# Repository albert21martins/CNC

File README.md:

# CNC
this is a project based on Cyclone PCB Factory https://github.com/carlosgs/Cyclone-PCB-Factory
Changed the hardware (MSP430) & Software. Add a 3.2"TFT User Interface and SD card in order to be independet from PC.
Still a lot to do. This is the first version and there are still some things to change in software.
You can find more information here:
http://e-homelab.flyvotech.com/index.php/2015/10/07/cnc-milling-machine/

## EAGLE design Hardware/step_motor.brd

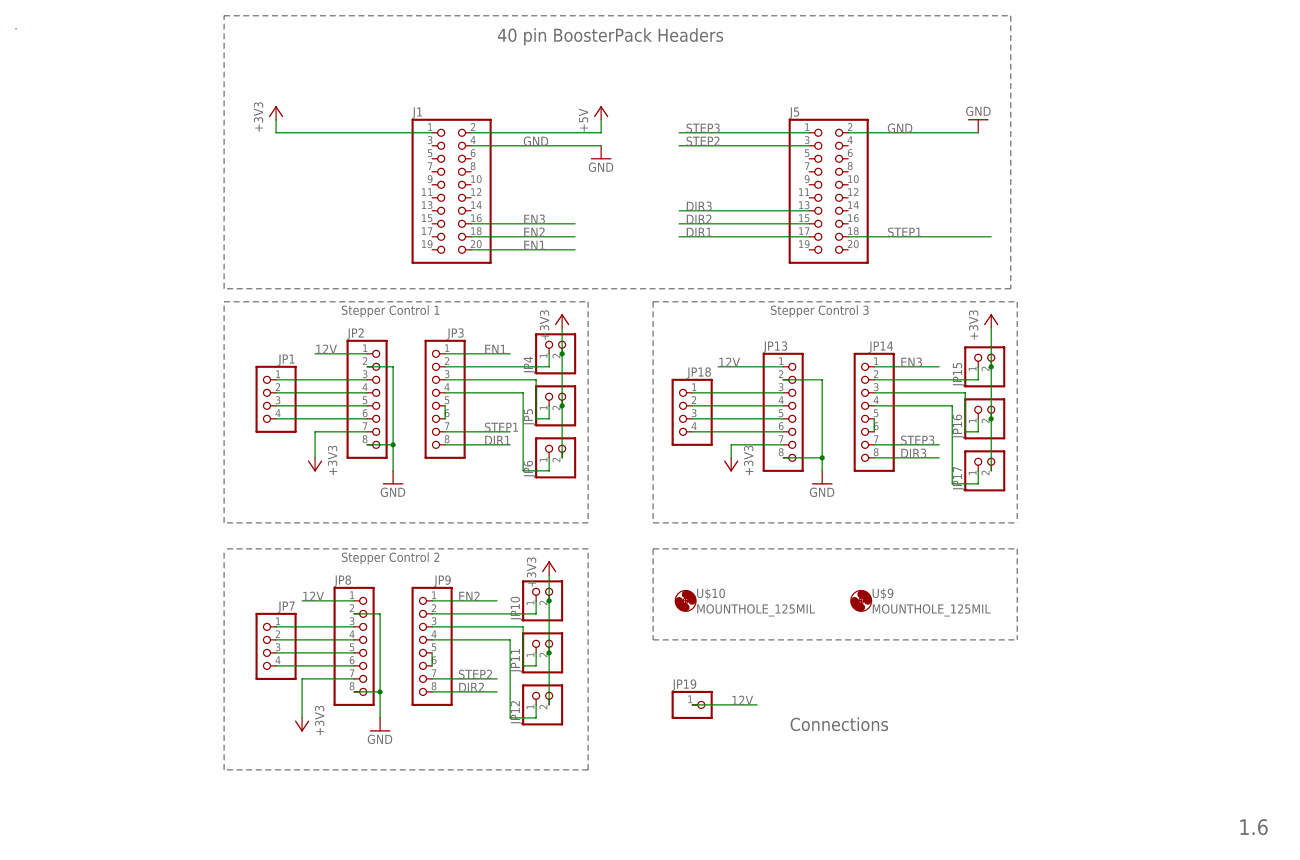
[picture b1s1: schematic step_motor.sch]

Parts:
J1, J5: PINHD-2X10; 2X10
JP1, JP7, JP18: PINHD-1X4; 1X04
JP2, JP3, JP8, JP9, JP13, JP14: PINHD-1X8; 1X08
JP4, JP5, JP6, JP10, JP11, JP12, JP15, JP16, JP17: PINHD-1X2; 1X02
JP19: PINHD-1X1; 1X01
U$4: MS_TM
U$9, U$10: MOUNTHOLE_125MIL

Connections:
12V: JP2.1, JP8.1, JP13.1, JP19.1
+5V: J1.2
DIR1: J5.17, JP3.8
DIR2: J5.15, JP9.8
DIR3: J5.13, JP14.8
EN1: J1.20, JP3.1
EN2: J1.18, JP9.1
EN3: J1.16, JP14.1
GND: J1.4, J5.2, JP2.2, JP2.8, JP8.2, JP8.8, JP13.2, JP13.8
unnamed: JP1.1, JP2.3
unnamed: JP1.2, JP2.4
unnamed: JP1.3, JP2.5
unnamed: JP1.4, JP2.6
unnamed: JP3.5, JP3.6
unnamed: JP3.2, JP4.1
unnamed: JP3.3, JP5.1
unnamed: JP3.4, JP6.1
unnamed: JP9.2, JP10.1
unnamed: JP9.3, JP11.1
unnamed: JP9.4, JP12.1
unnamed: JP7.1, JP8.3
unnamed: JP7.2, JP8.4
unnamed: JP9.5, JP9.6
unnamed: JP7.3, JP8.5
unnamed: JP7.4, JP8.6
unnamed: JP14.2, JP15.1
unnamed: JP14.3, JP16.1
unnamed: JP14.4, JP17.1
unnamed: JP14.5, JP14.6
unnamed: JP13.3, JP18.1
unnamed: JP13.4, JP18.2
unnamed: JP13.5, JP18.3
unnamed: JP13.6, JP18.4
STEP1: J5.18, JP3.7
STEP2: J5.3, JP9.7
STEP3: J5.1, JP14.7
VCC2: J1.1, JP2.7, JP4.2, JP5.2, JP6.2, JP8.7, JP10.2, JP11.2, JP12.2, JP13.7, JP15.2, JP16.2, JP17.2

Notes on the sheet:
40 pin BoosterPack Headers
Connections
1.6
Stepper Control 1
Stepper Control 2
Stepper Control 3

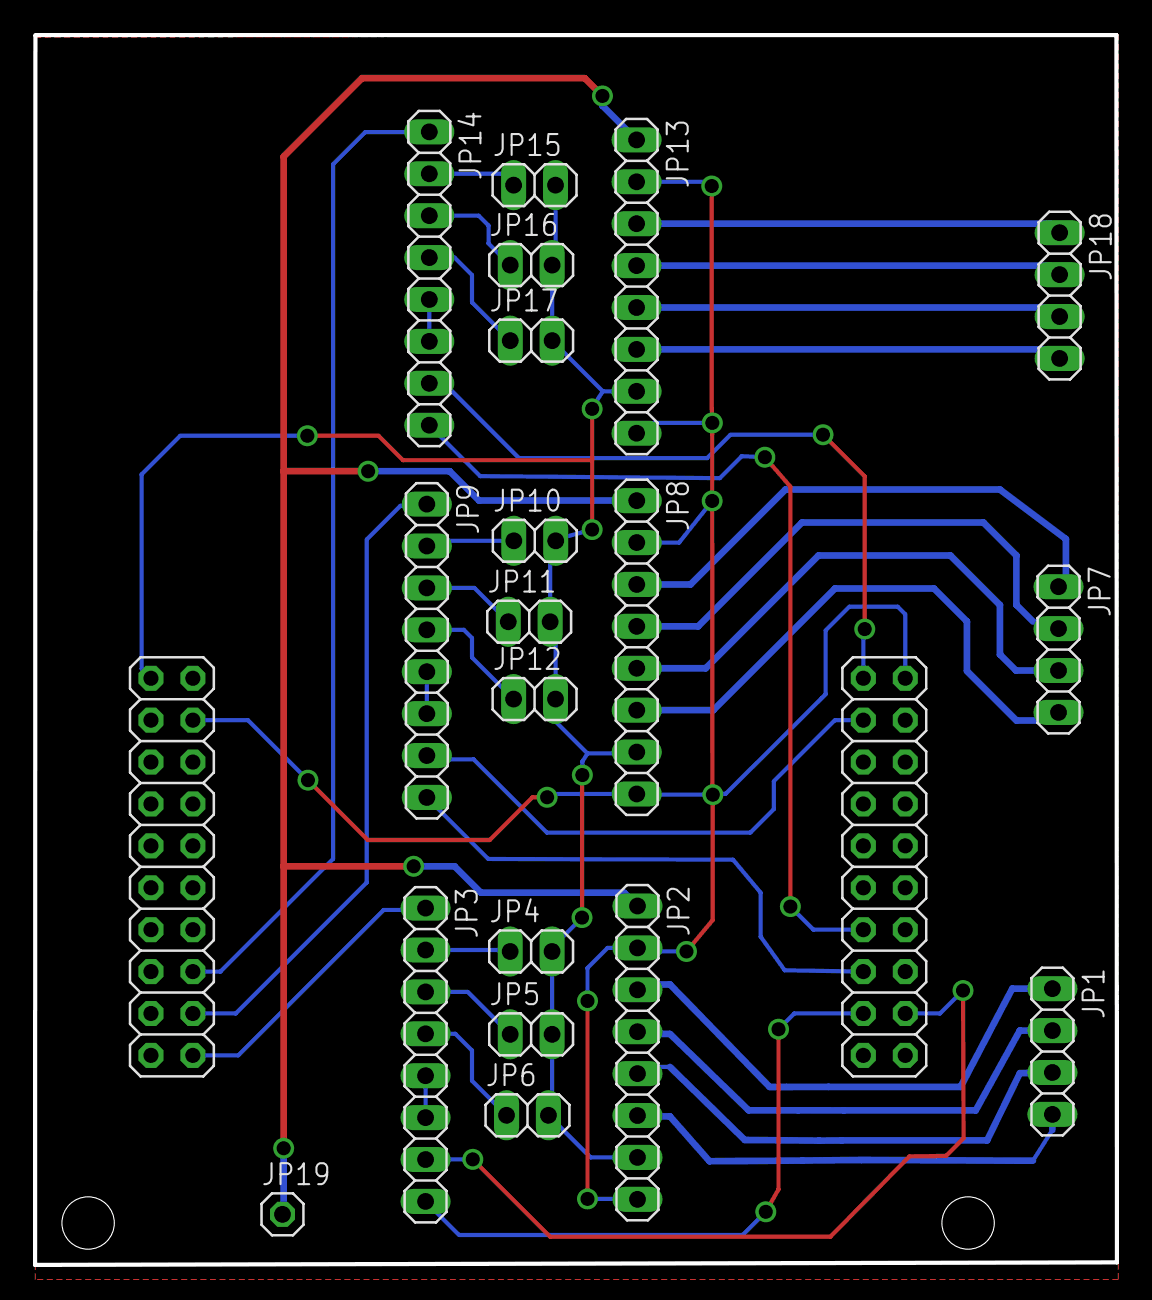
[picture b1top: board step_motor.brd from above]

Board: 2 copper layers, 65.6 x 74.5 mm, 24 parts (0 on the bottom side), 36 nets.

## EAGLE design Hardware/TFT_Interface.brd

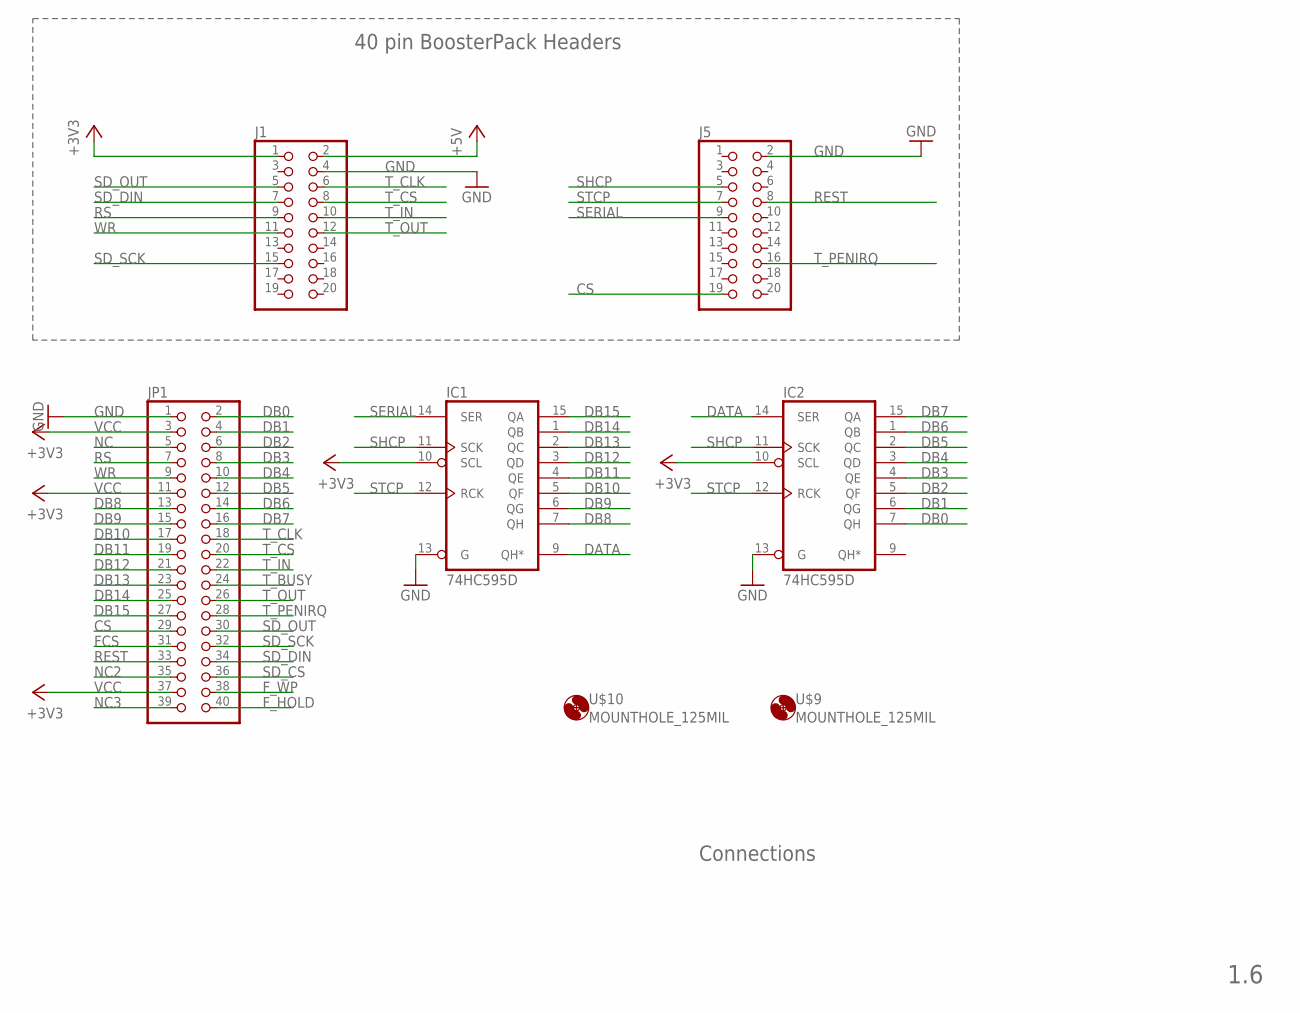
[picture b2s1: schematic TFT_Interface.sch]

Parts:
IC1, IC2: 74HC595D; SO16
J1, J5: PINHD-2X10; 2X10
JP1: PINHD-2X20; 2X20
U$9, U$10: MOUNTHOLE_125MIL

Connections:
+5V: J1.2
CS: J5.19, JP1.29
DATA: IC1.9 (QH*), IC2.14 (SER)
DB0: IC2.7 (QH), JP1.2
DB1: IC2.6 (QG), JP1.4
DB2: IC2.5 (QF), JP1.6
DB3: IC2.4 (QE), JP1.8
DB4: IC2.3 (QD), JP1.10
DB5: IC2.2 (QC), JP1.12
DB6: IC2.1 (QB), JP1.14
DB7: IC2.15 (QA), JP1.16
DB8: IC1.7 (QH), JP1.13
DB9: IC1.6 (QG), JP1.15
DB10: IC1.5 (QF), JP1.17
DB11: IC1.4 (QE), JP1.19
DB12: IC1.3 (QD), JP1.21
DB13: IC1.2 (QC), JP1.23
DB14: IC1.1 (QB), JP1.25
DB15: IC1.15 (QA), JP1.27
FCS: JP1.31
F_HOLD: JP1.40
F_WP: JP1.38
GND: IC1.8 (GND), IC1.13 (G), IC2.8 (GND), IC2.13 (G), J1.4, J5.2, JP1.1
NC: JP1.5
NC2: JP1.35
NC3: JP1.39
REST: J5.8, JP1.33
RS: J1.9, JP1.7
SD_CS: JP1.36
SD_DIN: J1.7, JP1.34
SD_OUT: J1.5, JP1.30
SD_SCK: J1.15, JP1.32
SERIAL: IC1.14 (SER), J5.9
SHCP: IC1.11 (SCK), IC2.11 (SCK), J5.5
STCP: IC1.12 (RCK), IC2.12 (RCK), J5.7
T_BUSY: JP1.24
T_CLK: J1.6, JP1.18
T_CS: J1.8, JP1.20
T_IN: J1.10, JP1.22
T_OUT: J1.12, JP1.26
T_PENIRQ: J5.16, JP1.28
VCC: IC1.10 (SCL), IC1.16 (VCC), IC2.10 (SCL), IC2.16 (VCC), J1.1, JP1.3, JP1.11, JP1.37
WR: J1.11, JP1.9

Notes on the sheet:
40 pin BoosterPack Headers
Connections
1.6

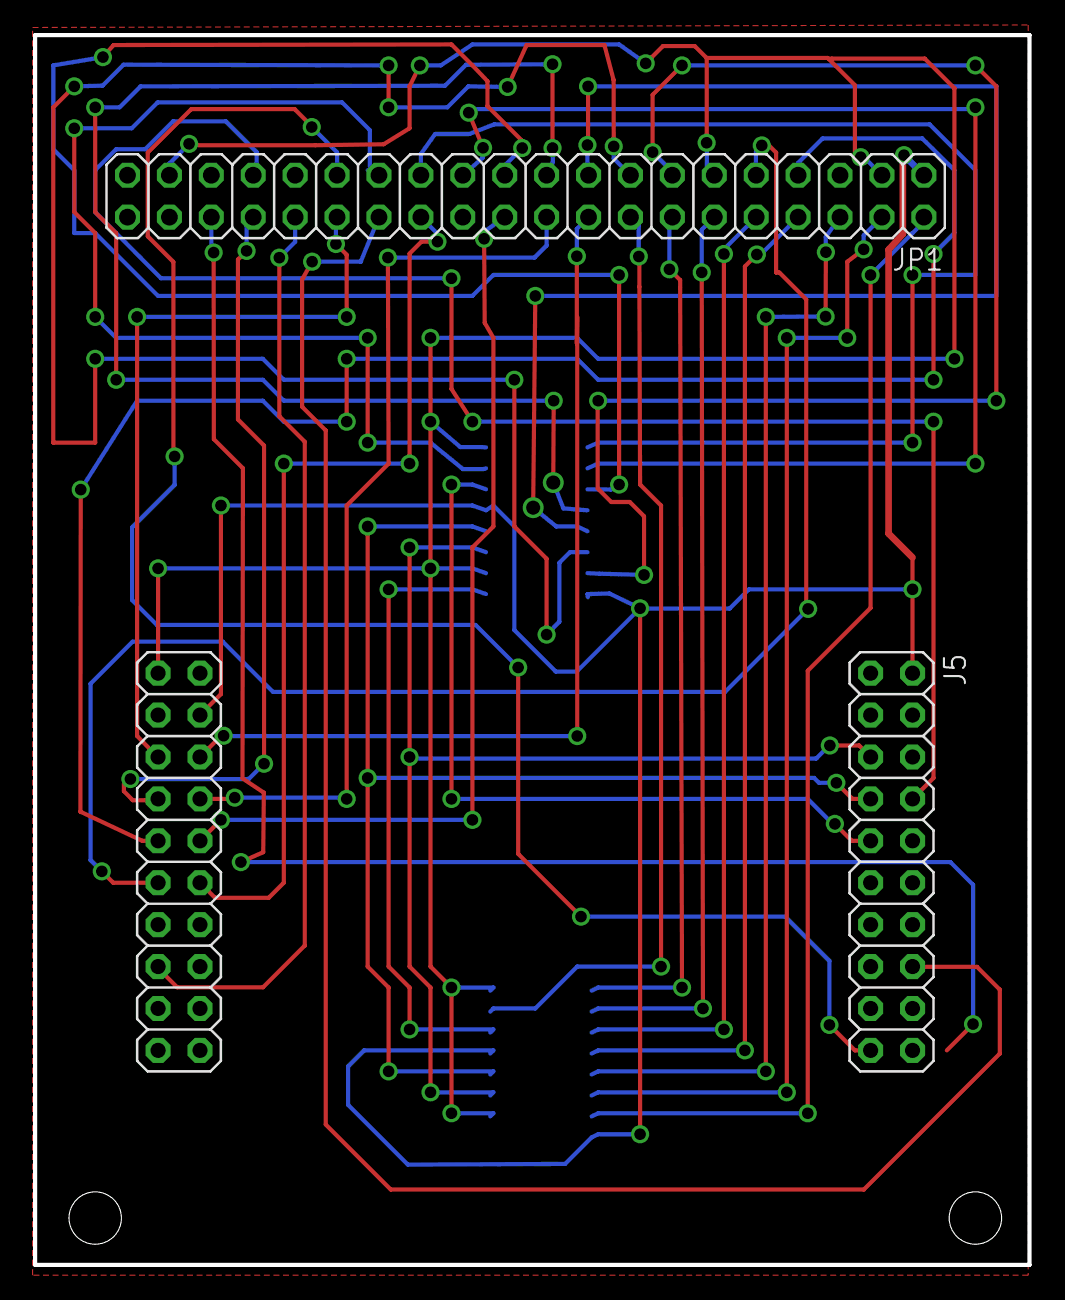
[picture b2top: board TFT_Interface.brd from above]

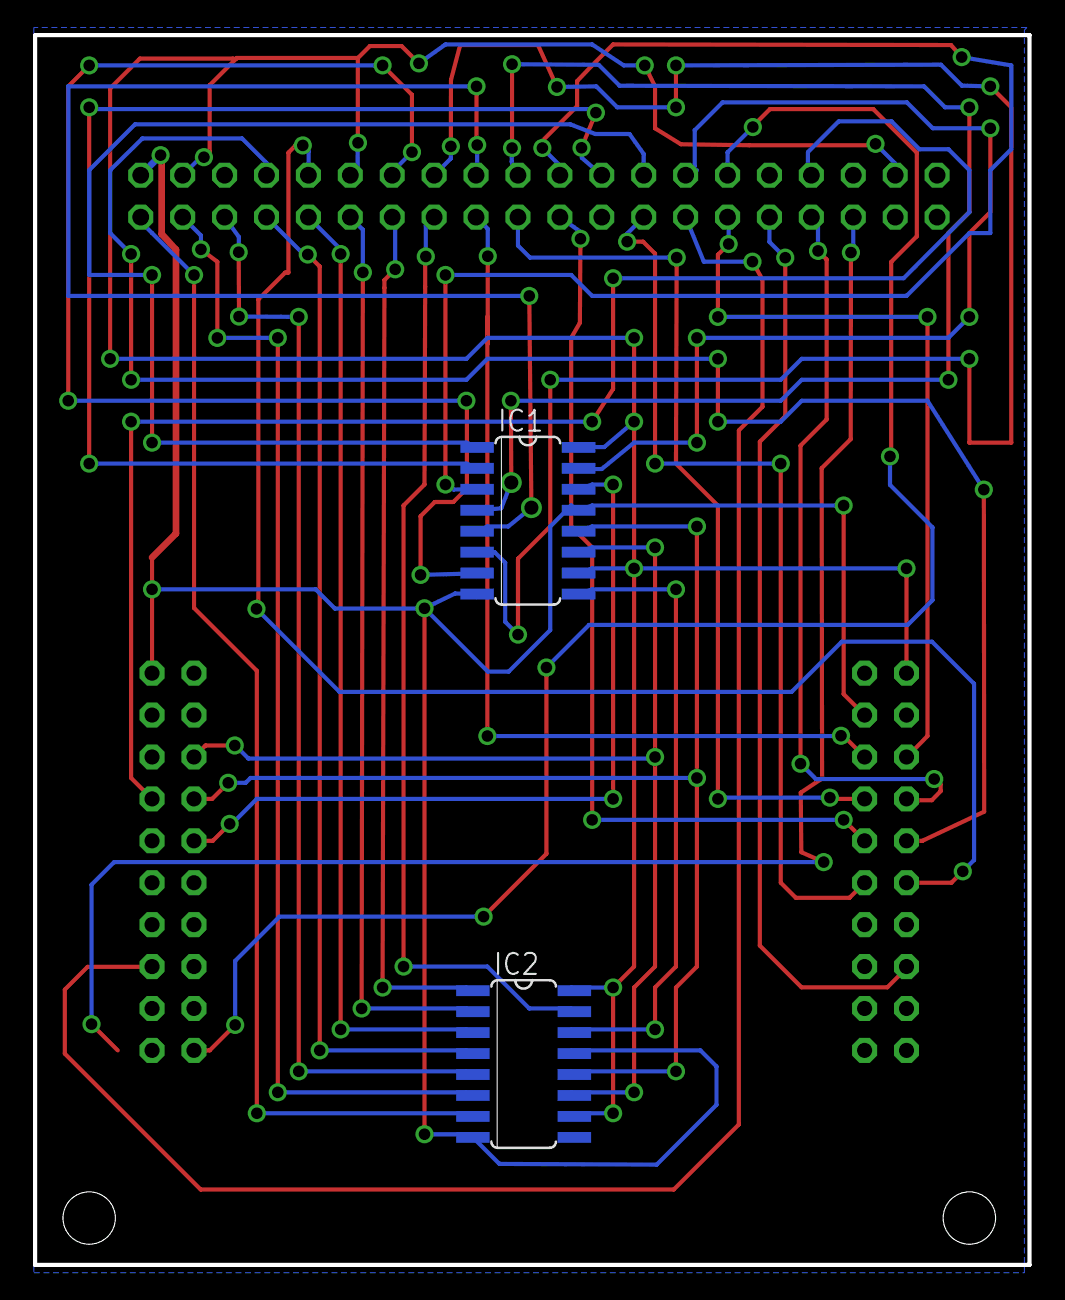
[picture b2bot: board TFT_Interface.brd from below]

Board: 2 copper layers, 60.3 x 74.5 mm, 7 parts (2 on the bottom side), 34 nets.

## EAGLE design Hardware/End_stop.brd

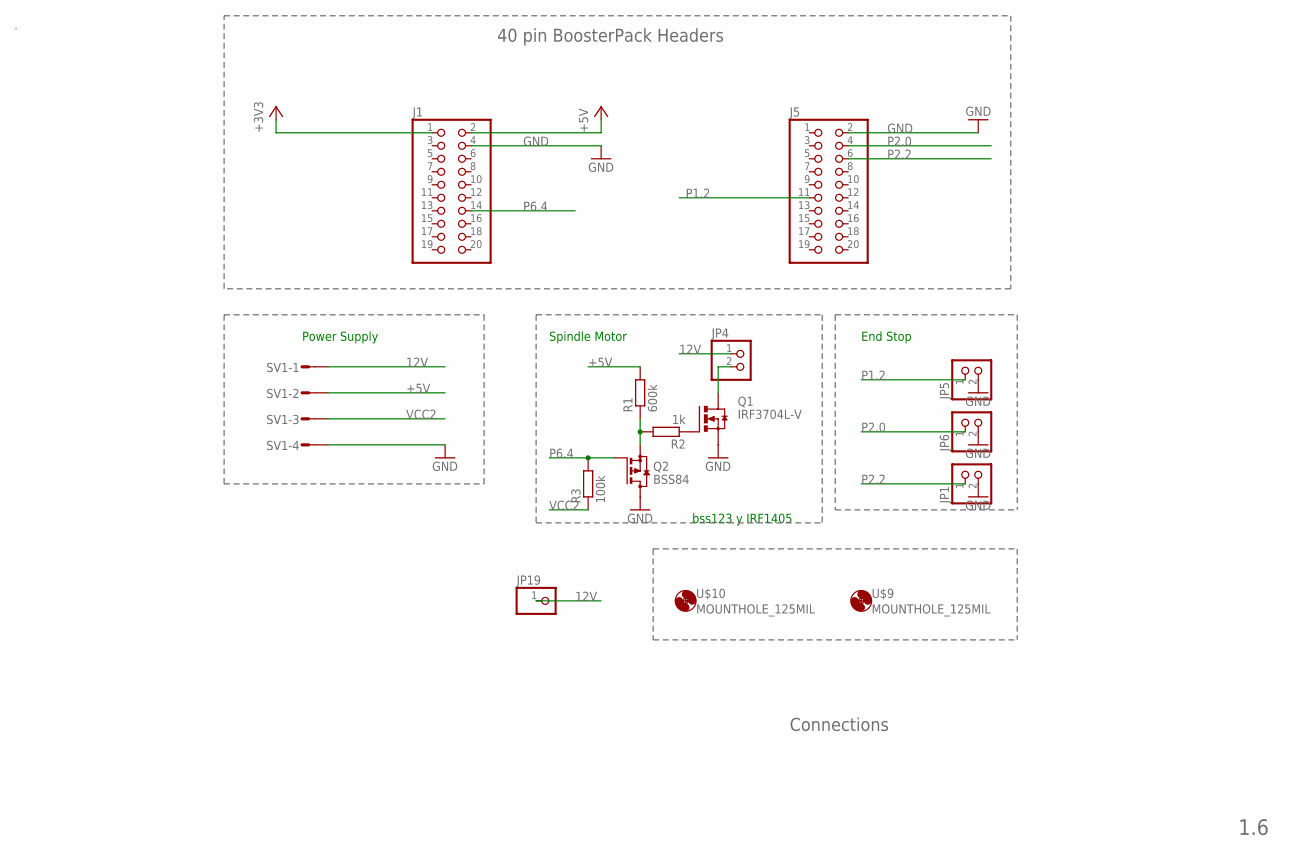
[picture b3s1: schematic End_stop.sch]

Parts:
J1, J5: PINHD-2X10; 2X10
JP1, JP4, JP5, JP6: PINHD-1X2; 1X02
JP19: PINHD-1X1; 1X01
Q1: IRF3704L-V; TO262-V
Q2: BSS84; SOT23
R1: 600k; R0603
R2: 1k; R0603
R3: 100k; R0603
SV1: MT6-4
U$4: MS_TM
U$9, U$10: MOUNTHOLE_125MIL

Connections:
12V: JP4.1, JP19.1, SV1.1
+5V: J1.2, R1.2, SV1.2
GND: J1.4, J5.2, JP1.2, JP5.2, JP6.2, Q1.3 (S), Q2.3 (D), SV1.4
unnamed: JP4.2, Q1.2 (D)
unnamed: Q1.1 (G), R2.1
unnamed: Q2.2 (S), R1.1, R2.2
P1.2: J5.11, JP5.1
P2.0: J5.4, JP6.1
P2.2: J5.6, JP1.1
P6.4: J1.14, Q2.1 (G), R3.2
VCC2: J1.1, R3.1, SV1.3

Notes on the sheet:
40 pin BoosterPack Headers
Connections
1.6
Power Supply
End Stop
Spindle Motor
bss123 y IRF1405

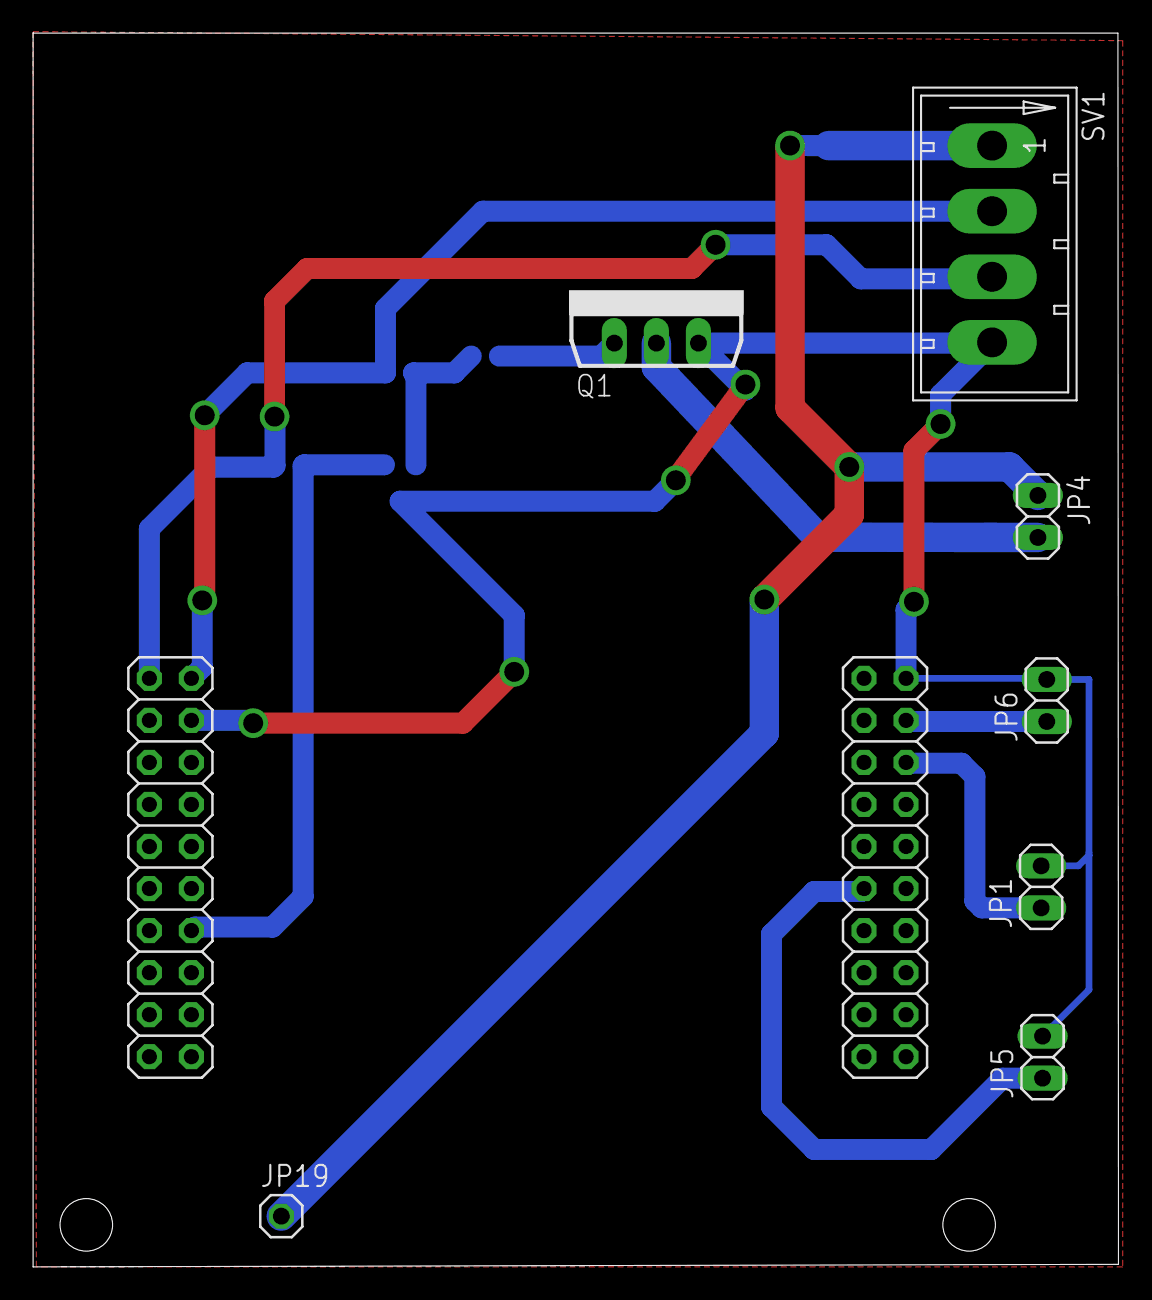
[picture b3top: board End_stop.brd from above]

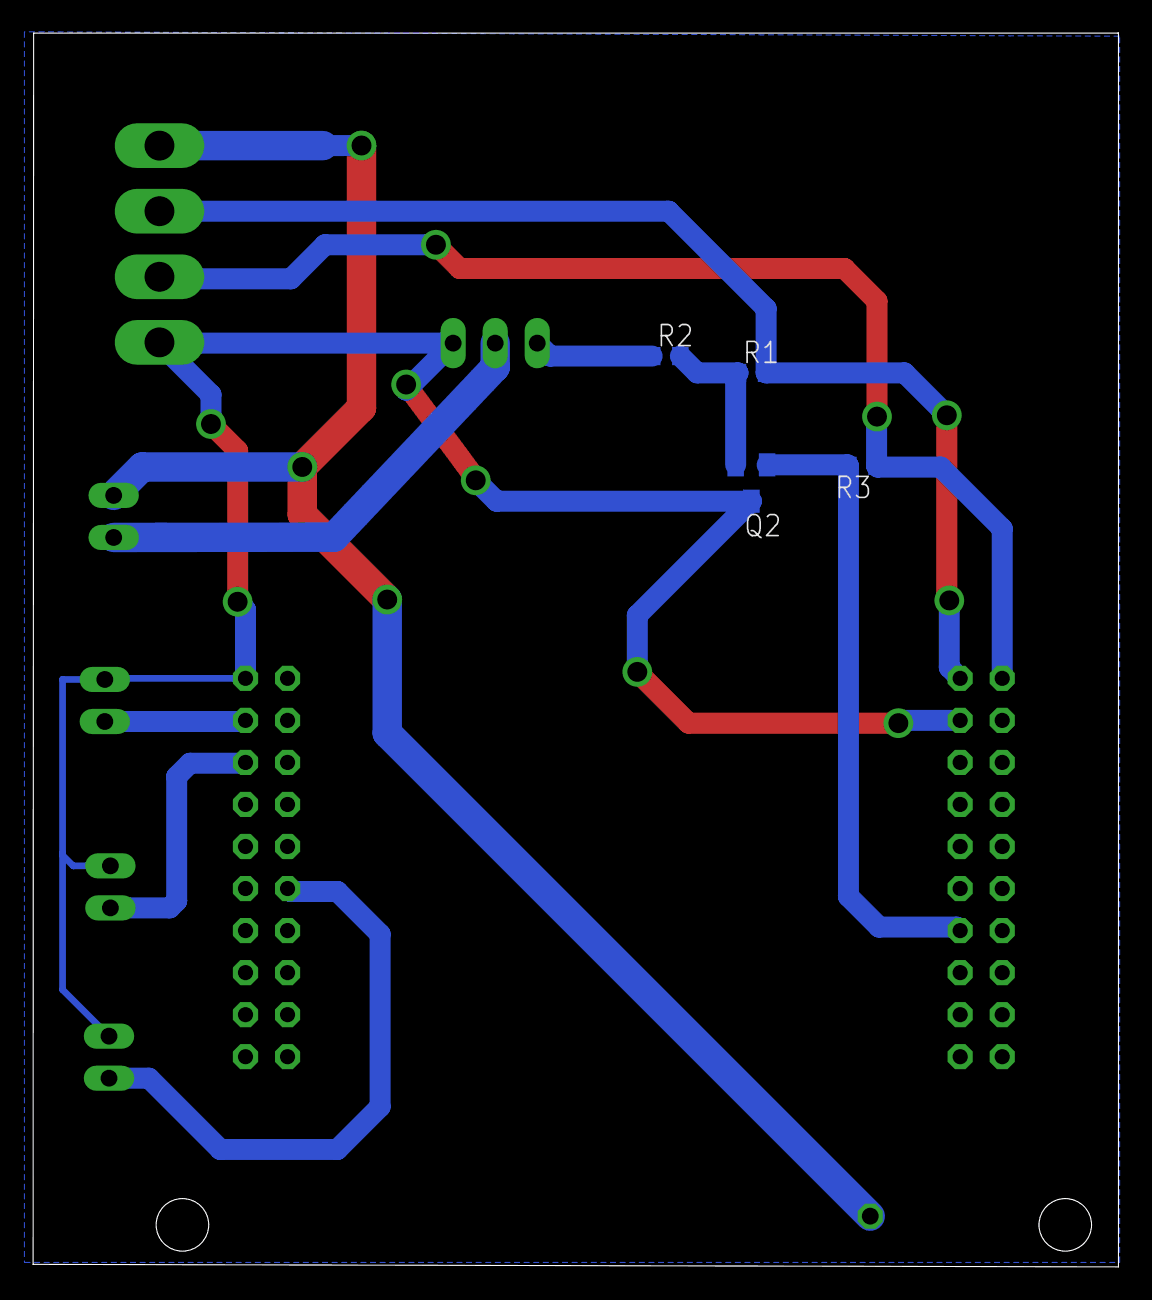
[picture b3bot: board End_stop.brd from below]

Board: 2 copper layers, 65.6 x 74.5 mm, 16 parts (4 on the bottom side), 11 nets.

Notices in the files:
Hardware/End_stop.brd:
(C)2003 A. DANNENBERG
